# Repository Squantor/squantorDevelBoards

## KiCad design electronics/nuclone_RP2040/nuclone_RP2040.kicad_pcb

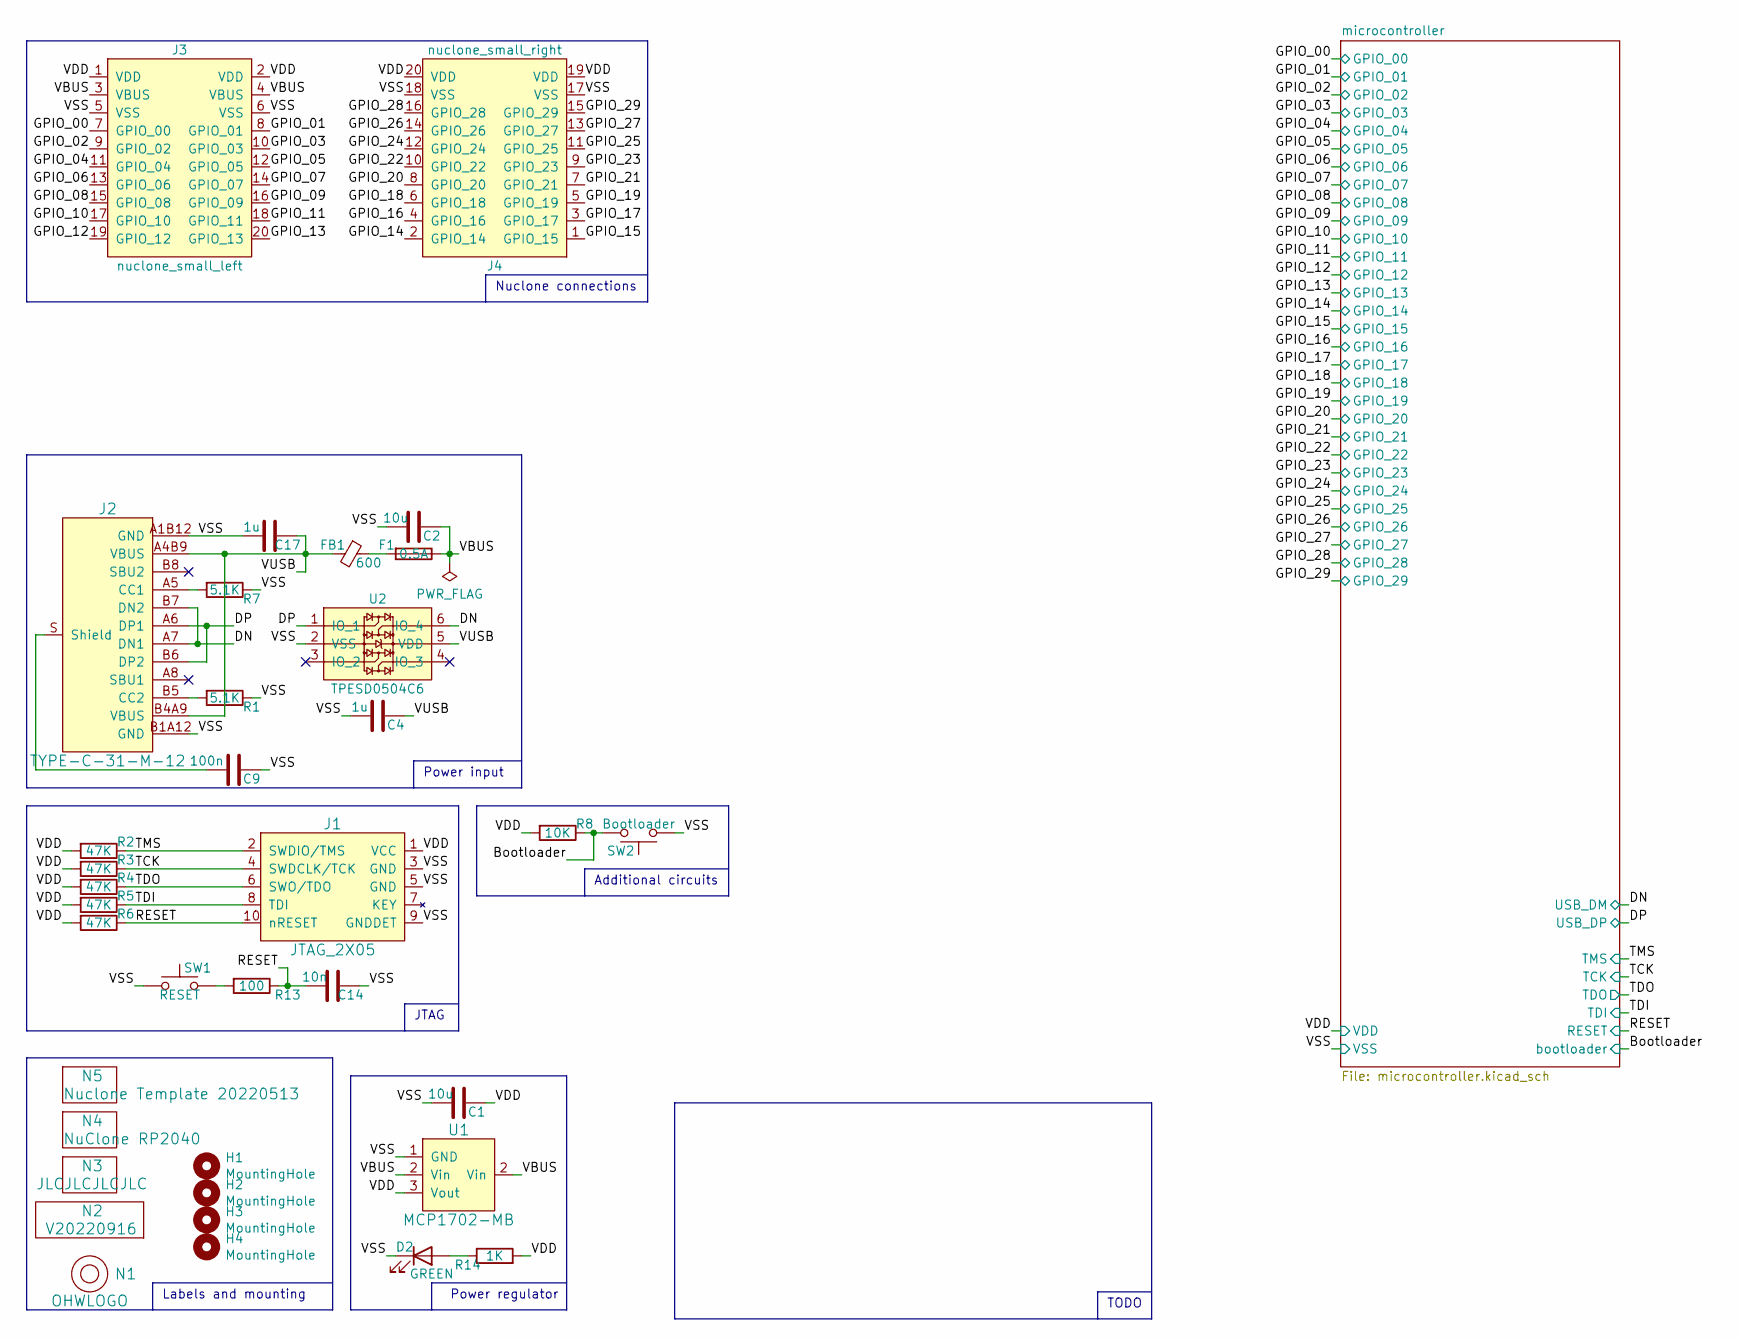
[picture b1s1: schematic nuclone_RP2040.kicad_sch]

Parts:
C1, C2: 10u; C_0603
C4: 1u; C_0402
C9: 100n; C_0805
C14: 10n; C_0402
C17: 1u; C_0603
D2: GREEN; LED_0603_hand
F1: 0.5A; F_0603_hand
FB1: 600; L_0603
H1, H2, H3, H4: MountingHole; MountingHole_3.2mm_M3_Pad_Via
J1: JTAG_2X05; Header-0127-2X05-H006
J2: TYPE-C-31-M-12; USB-C-HRO-31-M-12
J3: nuclone_small_left; nuclone_small_left_stacked
J4: nuclone_small_right; nuclone_small_right_stacked
N1: OHWLOGO; OSHW-Symbol_6.7x6mm_SilkScreen
N2: V20220916; Label_Generic
N3: JLCJLCJLCJLC; Label_Generic
N4: NuClone RP2040; Label_Generic
N5: Nuclone Template 20220513; Label_Generic
R1, R7: 5.1K; R_0402_hand
R2, R3, R4, R5, R6: 47K; R_0402_hand
R8: 10K; R_0402_hand
R13: 100; R_0402_hand
R14: 1K; R_0402_hand
SW1: RESET; TD-85XU
SW2: Bootloader; TD-85XU
U1: MCP1702-MB; SOT89-NXP
U2: TPESD0504C6; SOT363-ONsemi

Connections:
/Bootloader: R8.1, SW2.2; also elsewhere on the board
/DN: J2.A7 (DN1), J2.B7 (DN2), U2.6 (IO_4); also elsewhere on the board
/DP: J2.A6 (DP1), J2.B6 (DP2), U2.1 (IO_1); also elsewhere on the board
/GPIO_00: J3.7 (GPIO_00); also elsewhere on the board
/GPIO_01: J3.8 (GPIO_01); also elsewhere on the board
/GPIO_02: J3.9 (GPIO_02); also elsewhere on the board
/GPIO_03: J3.10 (GPIO_03); also elsewhere on the board
/GPIO_04: J3.11 (GPIO_04); also elsewhere on the board
/GPIO_05: J3.12 (GPIO_05); also elsewhere on the board
/GPIO_06: J3.13 (GPIO_06); also elsewhere on the board
/GPIO_07: J3.14 (GPIO_07); also elsewhere on the board
/GPIO_08: J3.15 (GPIO_08); also elsewhere on the board
/GPIO_09: J3.16 (GPIO_09); also elsewhere on the board
/GPIO_10: J3.17 (GPIO_10); also elsewhere on the board
/GPIO_11: J3.18 (GPIO_11); also elsewhere on the board
/GPIO_12: J3.19 (GPIO_12); also elsewhere on the board
/GPIO_13: J3.20 (GPIO_13); also elsewhere on the board
/GPIO_14: J4.2 (GPIO_14); also elsewhere on the board
/GPIO_15: J4.1 (GPIO_15); also elsewhere on the board
/GPIO_16: J4.4 (GPIO_16); also elsewhere on the board
/GPIO_17: J4.3 (GPIO_17); also elsewhere on the board
/GPIO_18: J4.6 (GPIO_18); also elsewhere on the board
/GPIO_19: J4.5 (GPIO_19); also elsewhere on the board
/GPIO_20: J4.8 (GPIO_20); also elsewhere on the board
/GPIO_21: J4.7 (GPIO_21); also elsewhere on the board
/GPIO_22: J4.10 (GPIO_22); also elsewhere on the board
/GPIO_23: J4.9 (GPIO_23); also elsewhere on the board
/GPIO_24: J4.12 (GPIO_24); also elsewhere on the board
/GPIO_25: J4.11 (GPIO_25); also elsewhere on the board
/GPIO_26: J4.14 (GPIO_26); also elsewhere on the board
/GPIO_27: J4.13 (GPIO_27); also elsewhere on the board
/GPIO_28: J4.16 (GPIO_28); also elsewhere on the board
/GPIO_29: J4.15 (GPIO_29); also elsewhere on the board
/RESET: C14.2, J1.10 (nRESET), R6.1, R13.1; also elsewhere on the board
/TCK: J1.4 (SWDCLK/TCK), R3.1; also elsewhere on the board
/TDI: J1.8 (TDI), R5.1
/TDO: J1.6 (SWO/TDO), R4.1
/TMS: J1.2 (SWDIO/TMS), R2.1; also elsewhere on the board
/VBUS: C2.2, F1.1, J3.3 (VBUS), J3.4 (VBUS), U1.2 (Vin)
/VDD: C1.1, J1.1 (VCC), J3.1 (VDD), J3.2 (VDD), J4.19 (VDD), J4.20 (VDD), R2.2, R3.2, R4.2, R5.2, R6.2, R8.2, R14.2, U1.3 (Vout); also elsewhere on the board
/VSS: C1.2, C2.1, C4.2, C9.1, C14.1, C17.1, D2.1 (K), J1.3 (GND), J1.5 (GND), J1.9 (GNDDET), J2.A1B12 (GND), J2.B1A12 (GND), J3.5 (VSS), J3.6 (VSS), J4.17 (VSS), J4.18 (VSS), R1.1, R7.1, SW1.1, SW2.1, U1.1 (GND), U2.2 (VSS); also elsewhere on the board
/VUSB: C4.1, C17.2, FB1.2, J2.A4B9 (VBUS), J2.B4A9 (VBUS), U2.5 (VDD)
unnamed: C9.2, J2.S (Shield)
unnamed: D2.2 (A), R14.1
unnamed: F1.2, FB1.1
unnamed: J2.A5 (CC1), R7.2
unnamed: J2.B5 (CC2), R1.2
unnamed: R13.2, SW1.2

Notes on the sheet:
JTAG
Power regulator
TODO
Additional circuits
Nuclone connections
Labels and mounting
Power input

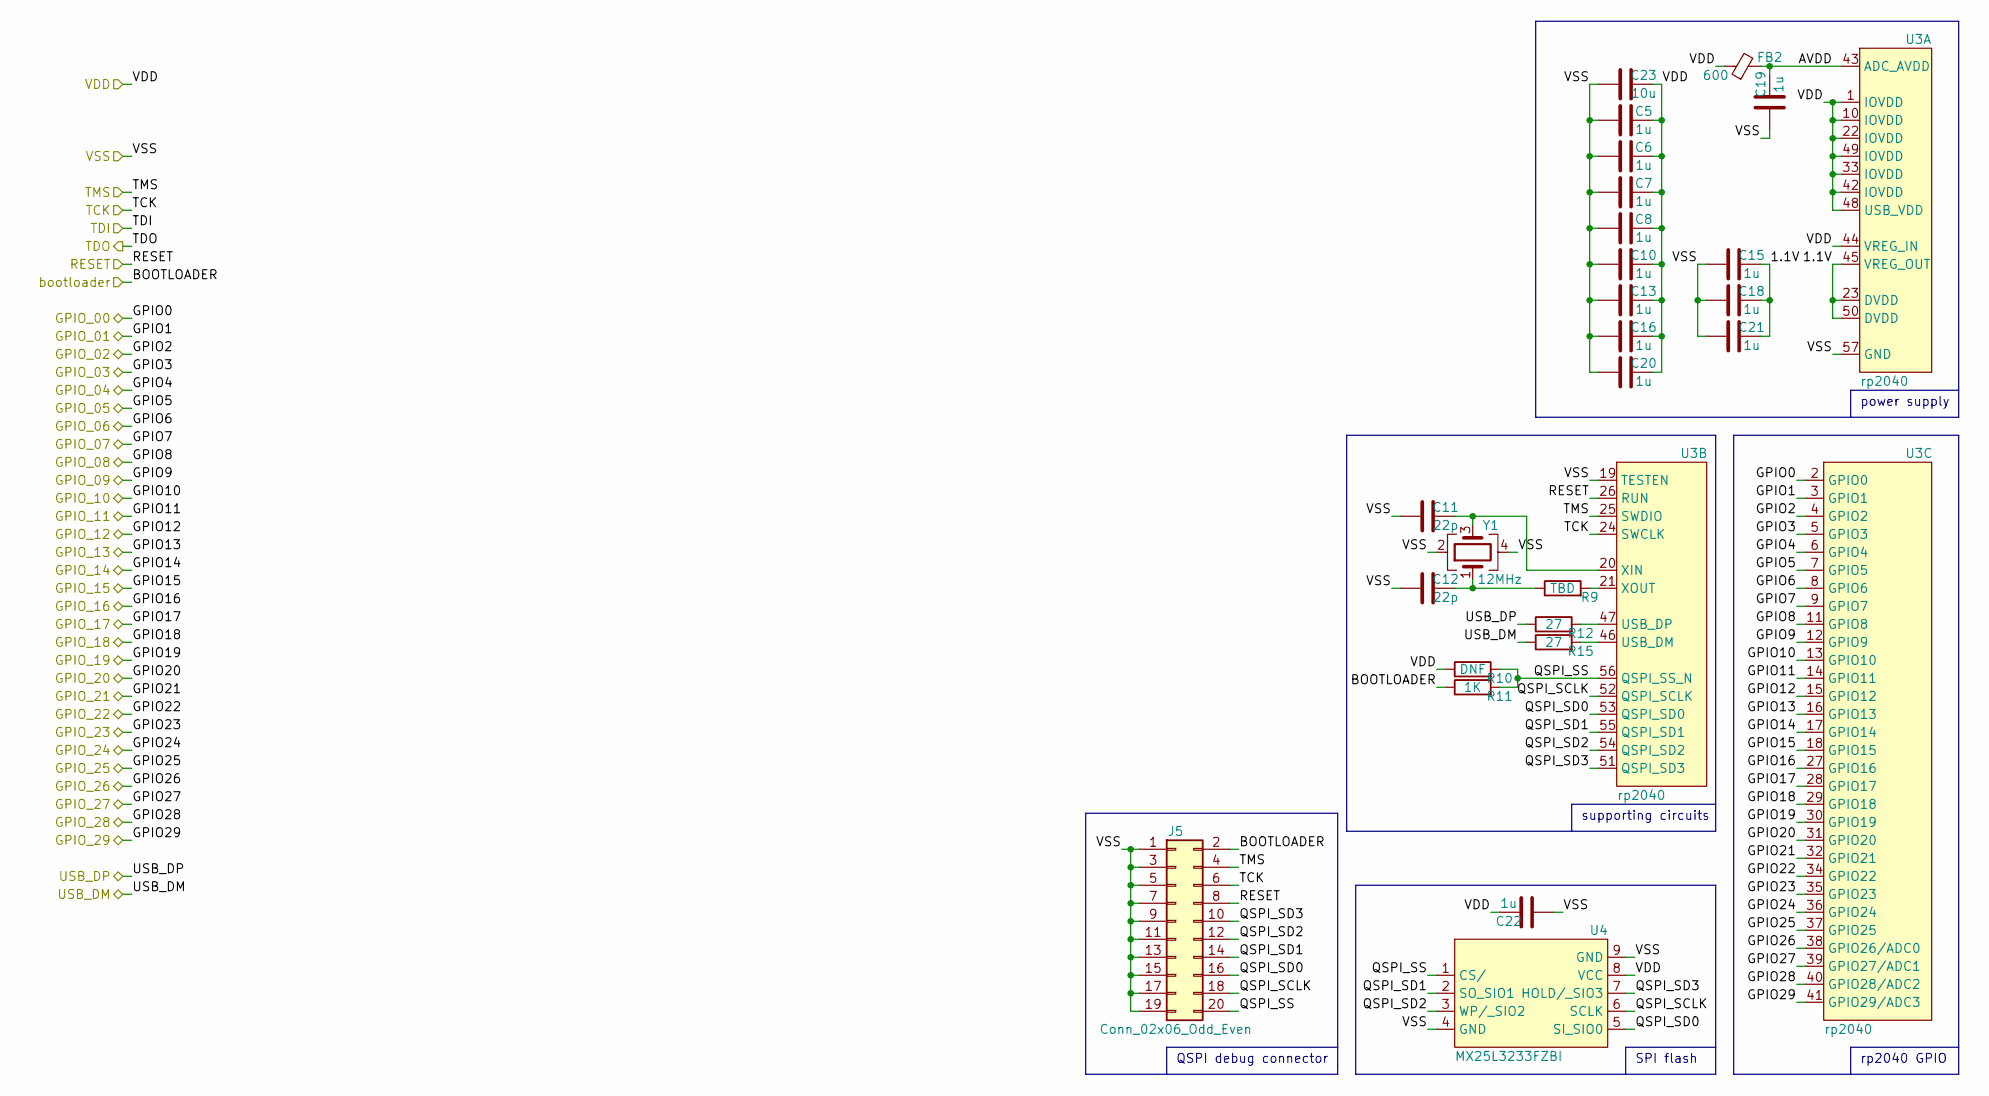
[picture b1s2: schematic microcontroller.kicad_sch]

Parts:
C5, C6, C7, C8, C10, C13, C15, C16, C18, C19, C20, C21, C22: 1u; C_0402
C11, C12: 22p; C_0402
C23: 10u; C_0603
FB2: 600; L_0402
J5: Conn_02x06_Odd_Even; Header-0127-2X10-H006
R9: TBD; R_0402_hand
R10: DNF; R_0402_hand
R11: 1K; R_0402_hand
R12, R15: 27; R_0402_hand
U3: rp2040; QFN56_7by7mm_RaspberryPi
U4: MX25L3233FZBI; USON-8-4x3-Macronix
Y1: 12MHz; Crystal_2520_4

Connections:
/Bootloader: J5.2, R11.1; also elsewhere on the board
/DN: R15.1; also elsewhere on the board
/DP: R12.1; also elsewhere on the board
/GPIO_00: U3.2 (GPIO0); also elsewhere on the board
/GPIO_01: U3.3 (GPIO1); also elsewhere on the board
/GPIO_02: U3.4 (GPIO2); also elsewhere on the board
/GPIO_03: U3.5 (GPIO3); also elsewhere on the board
/GPIO_04: U3.6 (GPIO4); also elsewhere on the board
/GPIO_05: U3.7 (GPIO5); also elsewhere on the board
/GPIO_06: U3.8 (GPIO6); also elsewhere on the board
/GPIO_07: U3.9 (GPIO7); also elsewhere on the board
/GPIO_08: U3.11 (GPIO8); also elsewhere on the board
/GPIO_09: U3.12 (GPIO9); also elsewhere on the board
/GPIO_10: U3.13 (GPIO10); also elsewhere on the board
/GPIO_11: U3.14 (GPIO11); also elsewhere on the board
/GPIO_12: U3.15 (GPIO12); also elsewhere on the board
/GPIO_13: U3.16 (GPIO13); also elsewhere on the board
/GPIO_14: U3.17 (GPIO14); also elsewhere on the board
/GPIO_15: U3.18 (GPIO15); also elsewhere on the board
/GPIO_16: U3.27 (GPIO16); also elsewhere on the board
/GPIO_17: U3.28 (GPIO17); also elsewhere on the board
/GPIO_18: U3.29 (GPIO18); also elsewhere on the board
/GPIO_19: U3.30 (GPIO19); also elsewhere on the board
/GPIO_20: U3.31 (GPIO20); also elsewhere on the board
/GPIO_21: U3.32 (GPIO21); also elsewhere on the board
/GPIO_22: U3.34 (GPIO22); also elsewhere on the board
/GPIO_23: U3.35 (GPIO23); also elsewhere on the board
/GPIO_24: U3.36 (GPIO24); also elsewhere on the board
/GPIO_25: U3.37 (GPIO25); also elsewhere on the board
/GPIO_26: U3.38 (GPIO26/ADC0); also elsewhere on the board
/GPIO_27: U3.39 (GPIO27/ADC1); also elsewhere on the board
/GPIO_28: U3.40 (GPIO28/ADC2); also elsewhere on the board
/GPIO_29: U3.41 (GPIO29/ADC3); also elsewhere on the board
/RESET: J5.8, U3.26 (RUN); also elsewhere on the board
/TCK: J5.6, U3.24 (SWCLK); also elsewhere on the board
/TMS: J5.4, U3.25 (SWDIO); also elsewhere on the board
/VDD: C5.2, C6.2, C7.2, C8.2, C10.2, C13.2, C16.2, C20.2, C22.2, C23.2, FB2.1, R10.1, U3.1 (IOVDD), U3.10 (IOVDD), U3.22 (IOVDD), U3.33 (IOVDD), U3.42 (IOVDD), U3.44 (VREG_IN), U3.48 (USB_VDD), U3.49 (IOVDD), U4.8 (VCC); also elsewhere on the board
/VSS: C5.1, C6.1, C7.1, C8.1, C10.1, C11.1, C12.1, C13.1, C15.1, C16.1, C18.1, C19.1, C20.1, C21.1, C22.1, C23.1, J5.1, J5.3, J5.5, J5.7, J5.9, J5.11, J5.13, J5.15, J5.17, J5.19, U3.19 (TESTEN), U3.57 (GND), U4.4 (GND), U4.9 (GND), Y1.2, Y1.4; also elsewhere on the board
/microcontroller/1.1V: C15.2, C18.2, C21.2, U3.23 (DVDD), U3.45 (VREG_OUT), U3.50 (DVDD)
/microcontroller/AVDD: C19.2, FB2.2, U3.43 (ADC_AVDD)
/microcontroller/QSPI_SCLK: J5.18, U3.52 (QSPI_SCLK), U4.6 (SCLK)
/microcontroller/QSPI_SD0: J5.16, U3.53 (QSPI_SD0), U4.5 (SI_SIO0)
/microcontroller/QSPI_SD1: J5.14, U3.55 (QSPI_SD1), U4.2 (SO_SIO1)
/microcontroller/QSPI_SD2: J5.12, U3.54 (QSPI_SD2), U4.3 (WP/_SIO2)
/microcontroller/QSPI_SD3: J5.10, U3.51 (QSPI_SD3), U4.7 (HOLD/_SIO3)
/microcontroller/QSPI_SS: J5.20, R10.2, R11.2, U3.56 (QSPI_SS_N), U4.1 (CS/)
unnamed: C11.2, U3.20 (XIN), Y1.3
unnamed: C12.2, R9.1, Y1.1
unnamed: R9.2, U3.21 (XOUT)
unnamed: R12.2, U3.47 (USB_DP)
unnamed: R15.2, U3.46 (USB_DM)

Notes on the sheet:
supporting circuits
power supply
QSPI debug connector
rp2040 GPIO
SPI flash

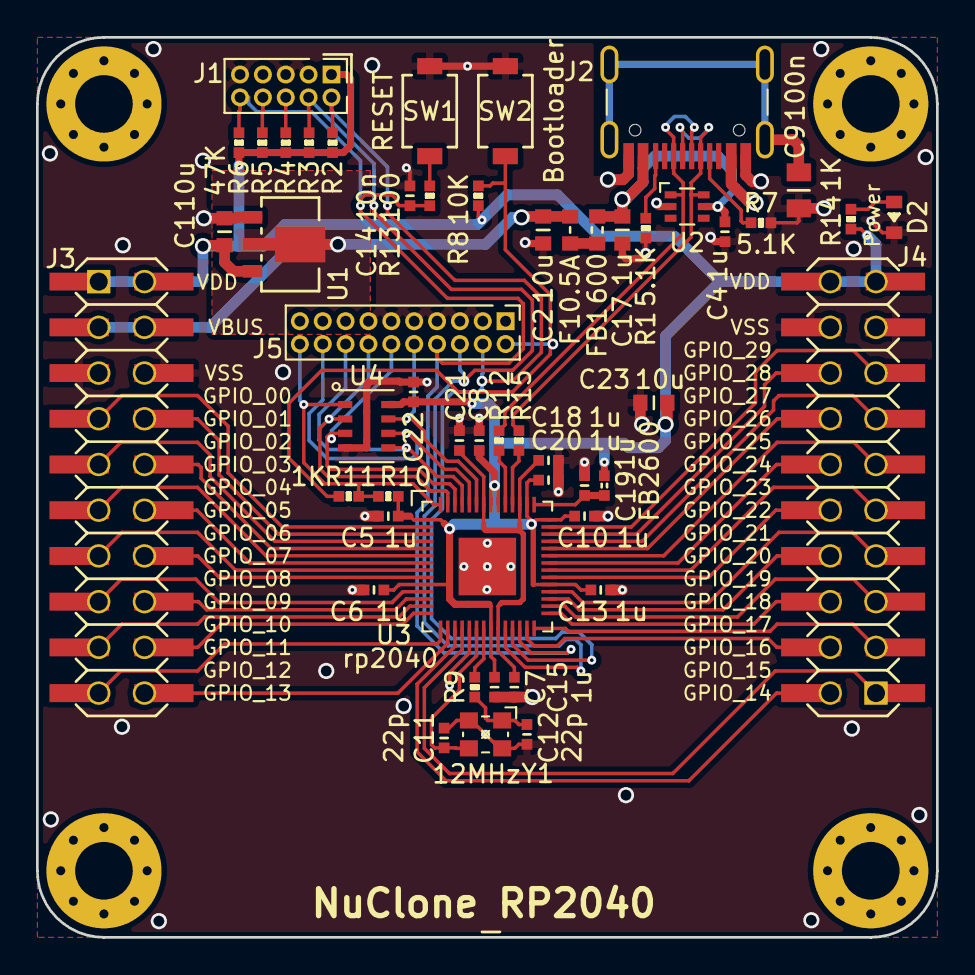
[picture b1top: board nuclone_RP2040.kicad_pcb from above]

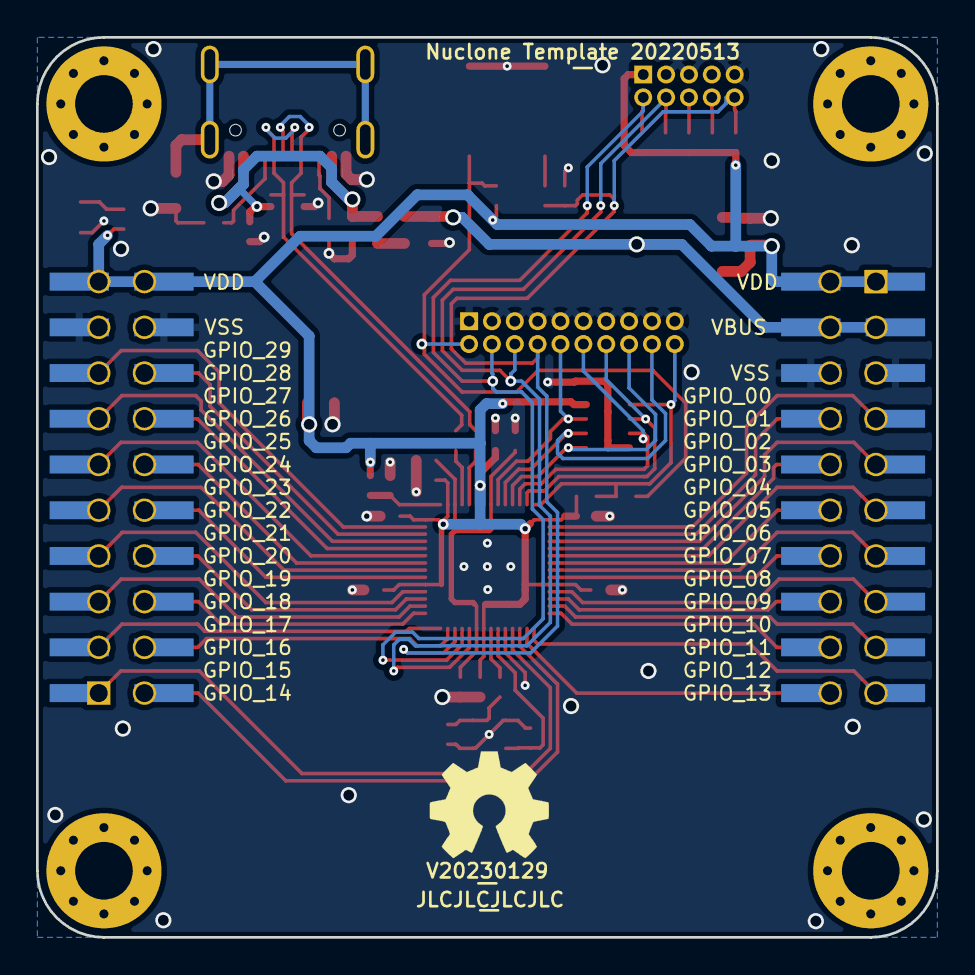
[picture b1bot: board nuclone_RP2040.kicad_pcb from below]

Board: 4 copper layers, 50.0 x 50.0 mm, 61 parts (4 on the bottom side), 61 nets.

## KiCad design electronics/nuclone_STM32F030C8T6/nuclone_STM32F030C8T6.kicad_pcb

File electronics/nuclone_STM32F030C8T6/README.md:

# STM32F030C8T6 nuclone board
Medium sized nuclone for the STM32F030C8T6 microcontroller
## TODO's
Still some things need to be done:
* schematic entry 
* PCB layout
* Review with one night in between
* Produce at [OSHPARK](https://oshpark.com/)
* Assemble
* Test & characterise
* update Readme.md with pictures and BOM

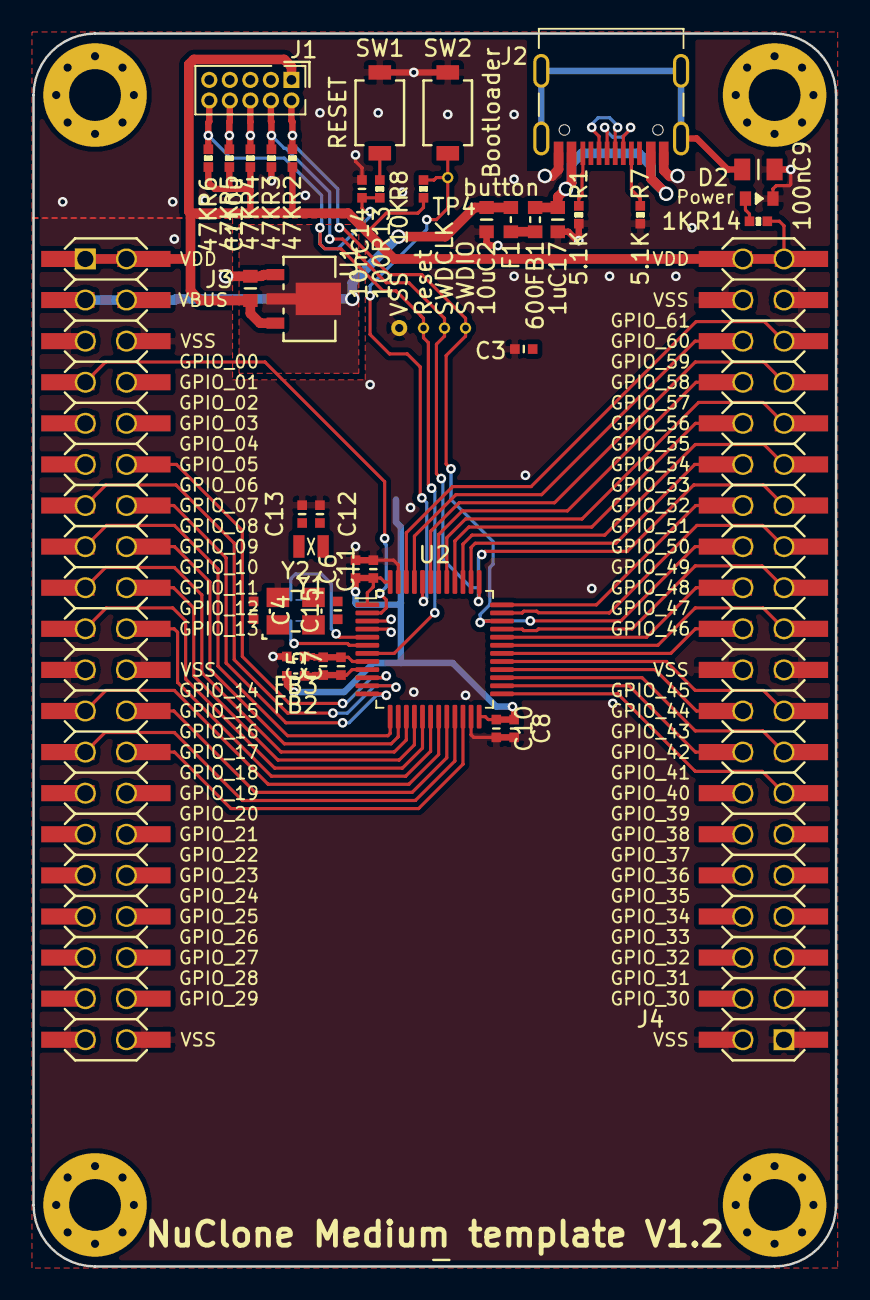
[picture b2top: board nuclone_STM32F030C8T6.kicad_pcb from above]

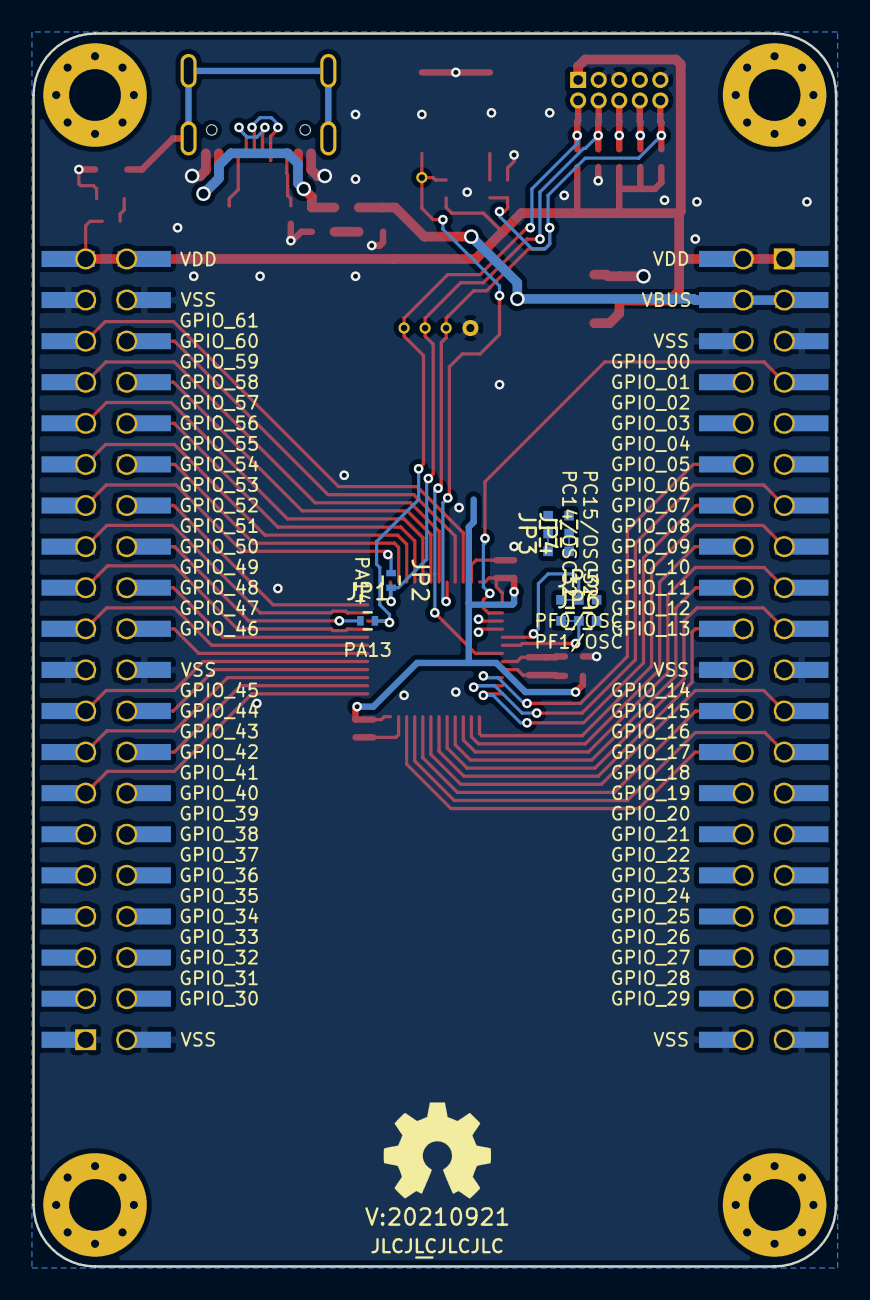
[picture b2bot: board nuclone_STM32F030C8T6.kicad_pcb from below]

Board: 2 copper layers, 49.6 x 76.2 mm, 60 parts (9 on the bottom side), 67 nets.

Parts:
C1, C2: 10u; C_0603
C3: 1u; C_0402
C4, C12, C13, C15: 10p; C_0402
C5, C6, C8: 100n; C_0402
C7, C10, C11, C14: 10n; C_0402
C9: 100n; C_0805
C17: 1u; C_0603
D2: GREEN; LED_0603_hand
F1: 0.5A; F_0603_hand
FB1: 600; L_0603
FB2, FB3: 600; L_0402
H1, H2, H3, H4: MountingHole; MountingHole_3.2mm_M3_Pad_Via
J1: JTAG_2X05; Header-0127-2X05-H006
J2: TYPE-C-31-M-12; USB-C-HRO-31-M-12
J3: nuclone_medium_left; nuclone_medium_left_stacked
J4: nuclone_medium_right; nuclone_medium_right_stacked
JP1: PA13; solder_jumper_2way_noconn
JP2: PA14; solder_jumper_2way_noconn
JP3: PC14/OSC32; solder_jumper_3way_12conn
JP4: PC15/OSC32; solder_jumper_3way_12conn
JP5: PF0/OSC; solder_jumper_3way_12conn
JP6: PF1/OSC; solder_jumper_3way_12conn
N1: OHWLOGO; OSHW-Symbol_6.7x6mm_SilkScreen
N2: 20210921; Label_version
N3: JLCJLCJLCJLC; Label_Generic
N4: NuClone Medium template V1.2; Label_Generic
R1, R7: 5.1K; R_0402_hand
R2, R3, R4, R5, R6: 47K; R_0402_hand
R8: 10K; R_0402_hand
R13: 100; R_0402_hand
R14: 1K; R_0402_hand
SW1: RESET; TD-85XU
SW2: Bootloader; TD-85XU
TP1: SWDIO; TestPoint_hole_H04R07
TP2: SWDCLK; TestPoint_hole_H04R07
TP3: VSS; TestPoint_hole_H05R10
TP4: button; TestPoint_hole_H04R07
TP5: Reset; TestPoint_hole_H04R07
U1: MCP1702-MB; SOT89-NXP
U2: STM32F030C8T6; LQFP-48_7x7mm_P0.5mm
Y1: 32KHz; Crystal_2012_2
Y2: 16MHz; Crystal_3225_4

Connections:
/Bootloader: R8.1, SW2.2, TP4.1, U2.44
/GPIO_00: J3.7, U2.2
/GPIO_01: J3.8, JP3.3
/GPIO_02: J3.9, JP4.3
/GPIO_03: J3.10, JP5.3
/GPIO_04: J3.11, JP6.3
/GPIO_05: J3.12, U2.10
/GPIO_06: J3.13, U2.11
/GPIO_07: J3.14, U2.12
/GPIO_08: J3.15, U2.13
/GPIO_09: J3.16, U2.14
/GPIO_10: J3.17, U2.15
/GPIO_11: J3.18, U2.16
/GPIO_12: J3.19, U2.17
/GPIO_13: J3.20, U2.18
/GPIO_14: J3.23, U2.19
/GPIO_15: J3.24, U2.20
/GPIO_16: J3.25, U2.21
/GPIO_17: J3.26, U2.22
/GPIO_41: J4.13, U2.25
/GPIO_42: J4.16, U2.26
/GPIO_43: J4.15, U2.27
/GPIO_44: J4.18, U2.28
/GPIO_45: J4.17, U2.29
/GPIO_46: J4.22, U2.30
/GPIO_47: J4.21, U2.31
/GPIO_48: J4.24, U2.32
/GPIO_49: J4.23, U2.33
/GPIO_50: J4.26, JP1.1
/GPIO_51: J4.25, U2.35
/GPIO_52: J4.28, U2.36
/GPIO_53: J4.27, JP2.1
/GPIO_54: J4.30, U2.38
/GPIO_55: J4.29, U2.39
/GPIO_56: J4.32, U2.40
/GPIO_57: J4.31, U2.41
/GPIO_58: J4.34, U2.42
/GPIO_59: J4.33, U2.43
/GPIO_60: J4.36, U2.45
/GPIO_61: J4.35, U2.46
/RESET: C14.2, J1.10, R6.1, R13.1, TP5.1, U2.7
/TCK: J1.4, JP2.2, R3.1, TP2.1, U2.37
/TDI: J1.8, R5.1
/TDO: J1.6, R4.1
/TMS: J1.2, JP1.2, R2.1, TP1.1, U2.34
/VBUS: C2.2, F1.1, J3.3, J3.4, U1.2
/VDD: C1.1, C3.1, C6.1, C8.1, C10.1, C11.1, FB2.2, J1.1, J3.1, J3.2, J4.39, J4.40, R2.2, R4.2, R5.2, R6.2, R8.2, R14.2, U1.3, U2.1, U2.24, U2.48
/VSS: C1.2, C2.1, C3.2, C4.1, C6.2, C8.2, C9.1, C10.2, C11.2, C12.1, C13.2, C14.1, C15.1, C17.1, D2.1, FB3.2, J1.3, J1.5, J1.9, J2.A1B12, J2.B1A12, J3.5, J3.6, J3.21, J3.22, J3.39, J3.40, J4.1, J4.2, J4.19, J4.20, J4.37, J4.38, R1.1, R3.2, R7.1, SW1.1, SW2.1, TP3.1, U1.1, U2.23, U2.47, Y2.2, Y2.4
/microcontroller/OSC32IN: C12.2, JP3.1, Y1.1
/microcontroller/OSC32IN_MCU: JP3.2, U2.3
/microcontroller/OSC32OUT: C13.1, JP4.1, Y1.2
/microcontroller/OSC32OUT_MCU: JP4.2, U2.4
/microcontroller/OSCIN: C4.2, JP5.1, Y2.1
/microcontroller/OSCIN_MCU: JP5.2, U2.5
/microcontroller/OSCOUT: C15.2, JP6.1, Y2.3
/microcontroller/OSCOUT_MCU: JP6.2, U2.6
/microcontroller/VDDA: C5.1, C7.1, FB2.1, U2.9
/microcontroller/VSSA: C5.2, C7.2, FB3.1, U2.8
unnamed: C9.2, J2.S
unnamed: C17.2, FB1.2, J2.A4B9, J2.B4A9
unnamed: D2.2, R14.1
unnamed: F1.2, FB1.1
unnamed: J2.A5, R7.2
unnamed: J2.A6, J2.B6
unnamed: J2.A7, J2.B7
unnamed: J2.B5, R1.2
unnamed: R13.2, SW1.2

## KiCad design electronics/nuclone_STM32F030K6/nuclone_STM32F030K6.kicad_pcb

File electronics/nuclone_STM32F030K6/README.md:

# Nuclone development board for STM32F030K6
STM32F030K6 development board inspired by the nucleo series from STM32.
## TODO's
Still some things need to be done:
* Review with one night in between (Done)
* Produce at [JLCPCB](https://jlcpcb.com/) (Done)
* Assemble (Done)
* Test & characterise (WIP)
* update Readme.md with pictures and BOM (WIP)

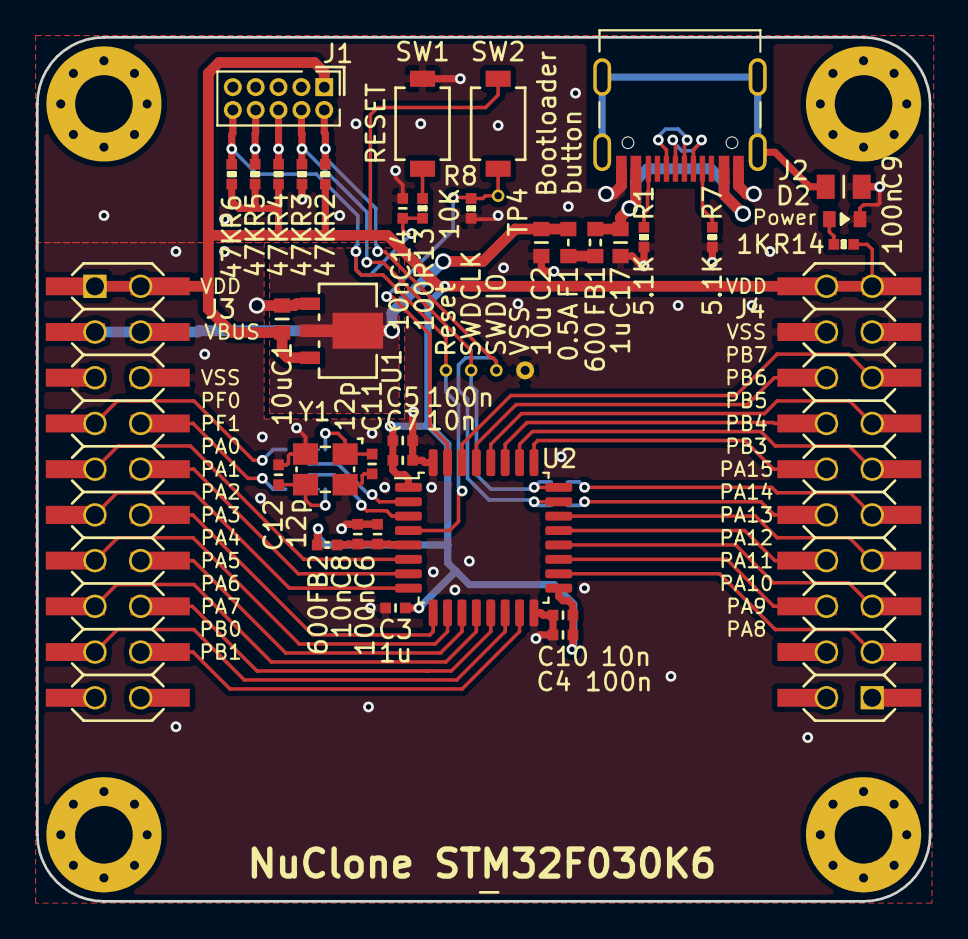
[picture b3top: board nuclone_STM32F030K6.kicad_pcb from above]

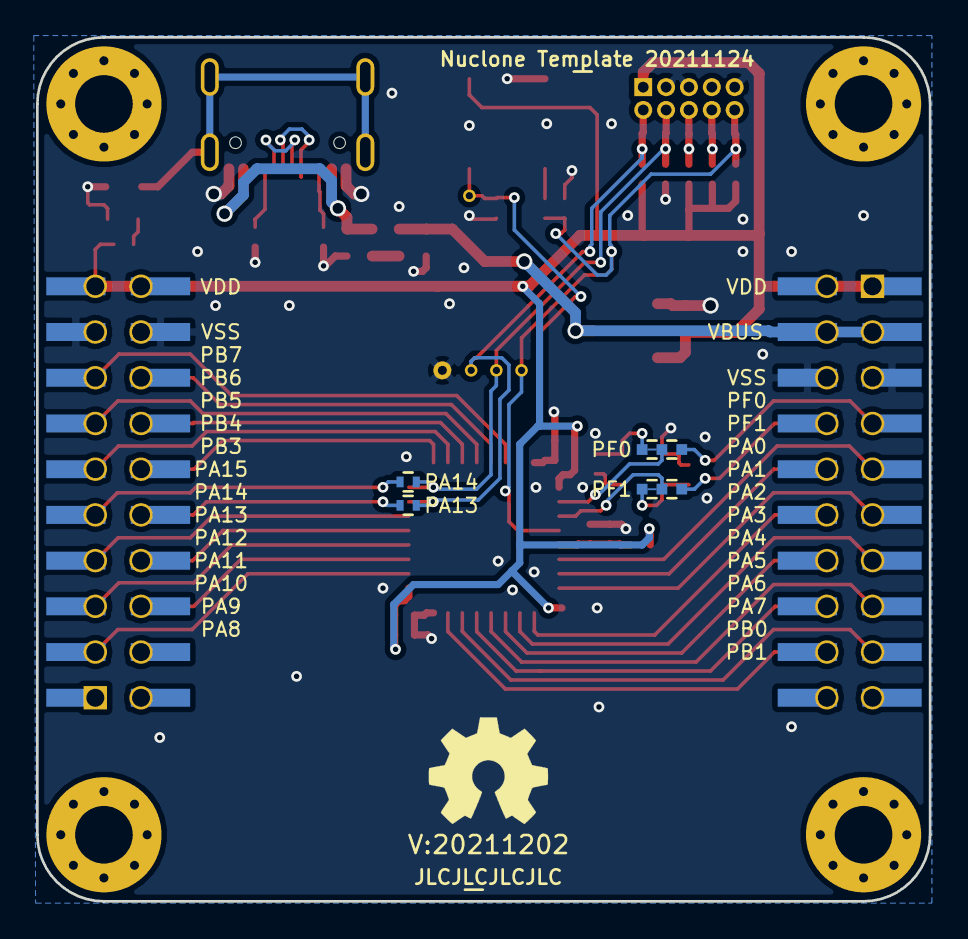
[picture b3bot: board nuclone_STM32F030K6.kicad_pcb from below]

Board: 2 copper layers, 49.6 x 48.0 mm, 55 parts (8 on the bottom side), 48 nets.

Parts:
C1, C2: 10u; C_0603
C3: 1u; C_0402
C4, C5, C6: 100n; C_0402
C7, C8, C10, C14: 10n; C_0402
C9: 100n; C_0805
C11, C12: 12p; C_0402
C17: 1u; C_0603
D2: GREEN; LED_0603_hand
F1: 0.5A; F_0603_hand
FB1: 600; L_0603
FB2: 600; L_0402
H1, H2, H3, H4: MountingHole; MountingHole_3.2mm_M3_Pad_Via
J1: JTAG_2X05; Header-0127-2X05-H006
J2: TYPE-C-31-M-12; USB-C-HRO-31-M-12
J3: nuclone_small_left; nuclone_small_left_stacked
J4: nuclone_small_right; nuclone_small_right_stacked
JP1: PA13; solder_jumper_2way_noconn
JP2: PA14; solder_jumper_2way_noconn
JP3: PF0; solder_jumper_3way_12conn
JP4: PF1; solder_jumper_3way_12conn
N1: OHWLOGO; OSHW-Symbol_6.7x6mm_SilkScreen
N2: 20211202; Label_version
N3: JLCJLCJLCJLC; Label_Generic
N4: NuClone STM32F030K6; Label_Generic
N5: Nuclone Template 20211124; Label_Generic
R1, R7: 5.1K; R_0402_hand
R2, R3, R4, R5, R6: 47K; R_0402_hand
R8: 10K; R_0402_hand
R13: 100; R_0402_hand
R14: 1K; R_0402_hand
SW1: RESET; TD-85XU
SW2: Bootloader; TD-85XU
TP1: SWDIO; TestPoint_hole_H04R07
TP2: SWDCLK; TestPoint_hole_H04R07
TP3: VSS; TestPoint_hole_H05R10
TP4: button; TestPoint_hole_H04R07
TP5: Reset; TestPoint_hole_H04R07
U1: MCP1702-MB; SOT89-NXP
U2: STM32F030K6; LQFP-32_7x7mm_P0.8mm
Y1: 16MHz; Crystal_3225_4

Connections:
/Bootloader: R8.1, SW2.2, TP4.1, U2.31
/GPIO_00: J3.7, JP3.3
/GPIO_01: J3.8, JP4.3
/GPIO_02: J3.9, U2.6
/GPIO_03: J3.10, U2.7
/GPIO_04: J3.11, U2.8
/GPIO_05: J3.12, U2.9
/GPIO_06: J3.13, U2.10
/GPIO_07: J3.14, U2.11
/GPIO_08: J3.15, U2.12
/GPIO_09: J3.16, U2.13
/GPIO_10: J3.17, U2.14
/GPIO_11: J3.18, U2.15
/GPIO_17: J4.3, U2.18
/GPIO_18: J4.6, U2.19
/GPIO_19: J4.5, U2.20
/GPIO_20: J4.8, U2.21
/GPIO_21: J4.7, U2.22
/GPIO_22: J4.10, JP1.1
/GPIO_23: J4.9, JP2.1
/GPIO_24: J4.12, U2.25
/GPIO_25: J4.11, U2.26
/GPIO_26: J4.14, U2.27
/GPIO_27: J4.13, U2.28
/GPIO_28: J4.16, U2.29
/GPIO_29: J4.15, U2.30
/RESET: C14.2, J1.10, R6.1, R13.1, TP5.1, U2.4
/TCK: J1.4, JP2.2, R3.1, TP2.1, U2.24
/TDI: J1.8, R5.1
/TDO: J1.6, R4.1
/TMS: J1.2, JP1.2, R2.1, TP1.1, U2.23
/VBUS: C2.2, F1.1, J3.3, J3.4, U1.2
/VDD: C1.1, C3.1, C4.1, C5.1, C7.1, C10.1, FB2.2, J1.1, J3.1, J3.2, J4.19, J4.20, R2.2, R4.2, R5.2, R6.2, R14.2, SW2.1, U1.3, U2.1, U2.17
/VSS: C1.2, C2.1, C3.2, C4.2, C5.2, C6.2, C7.2, C8.2, C9.1, C10.2, C11.2, C12.2, C14.1, C17.1, D2.1, J1.3, J1.5, J1.9, J2.A1B12, J2.B1A12, J3.5, J3.6, J4.17, J4.18, R1.1, R3.2, R7.1, R8.2, SW1.1, TP3.1, U1.1, U2.16, U2.32, Y1.2, Y1.4
/microcontroller/OSCIN: JP3.2, U2.2
/microcontroller/OSCOUT: JP4.2, U2.3
/microcontroller/VDDA: C6.1, C8.1, FB2.1, U2.5
unnamed: C9.2, J2.S
unnamed: C11.1, JP3.1, Y1.1
unnamed: C12.1, JP4.1, Y1.3
unnamed: C17.2, FB1.2, J2.A4B9, J2.B4A9
unnamed: D2.2, R14.1
unnamed: F1.2, FB1.1
unnamed: J2.A5, R7.2
unnamed: J2.A6, J2.B6
unnamed: J2.A7, J2.B7
unnamed: J2.B5, R1.2
unnamed: R13.2, SW1.2
